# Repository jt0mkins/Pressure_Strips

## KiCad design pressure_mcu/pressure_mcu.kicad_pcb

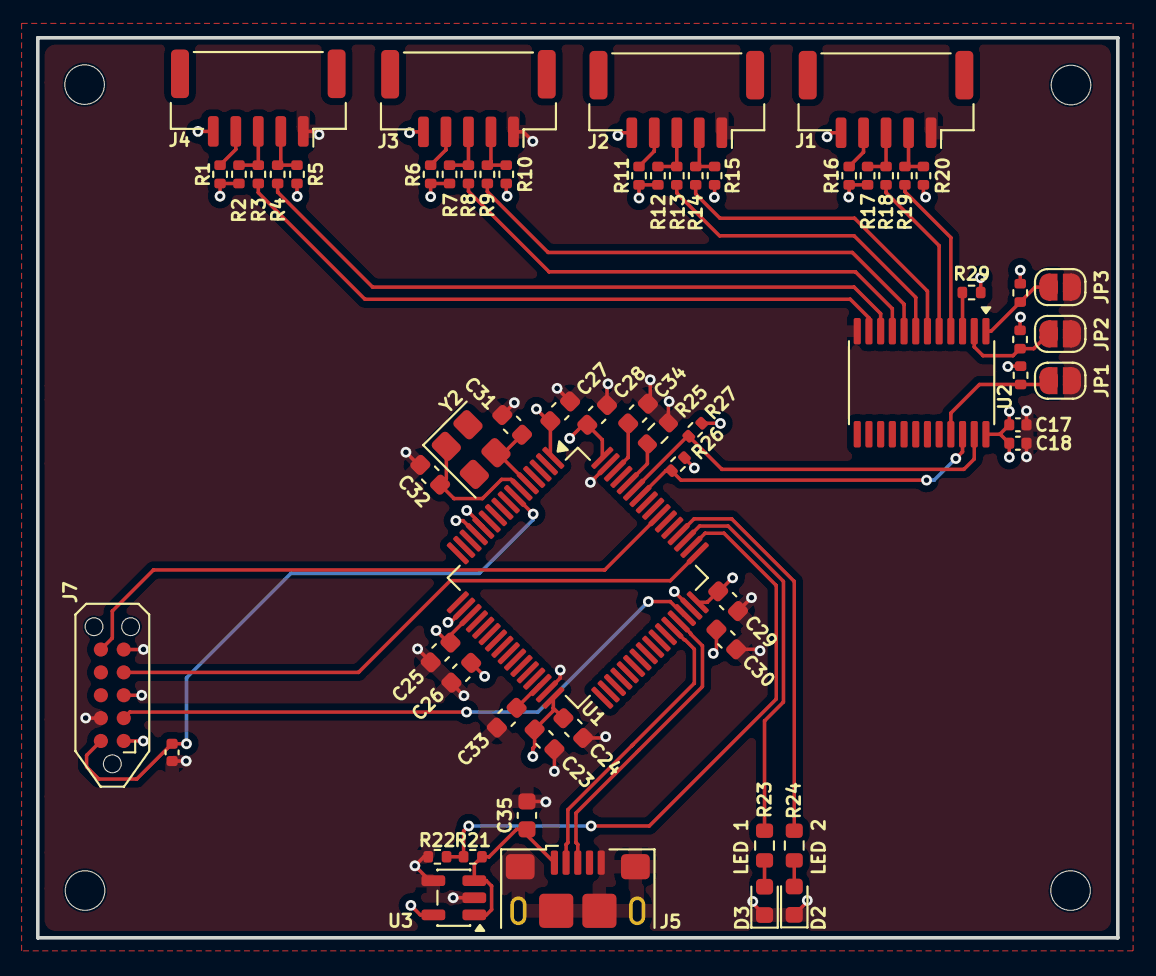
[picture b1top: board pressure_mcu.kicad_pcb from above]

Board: 4 copper layers, 60.0 x 50.0 mm, 66 parts (0 on the bottom side), 45 nets.

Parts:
C17: 4.7uF; C_0402_1005Metric
C18, C36: 100nF; C_0402_1005Metric
C23, C25, C27, C29: 100nF; C_0603_1608Metric
C24, C26, C28, C30: 4.7uF; C_0603_1608Metric
C31, C32: 33pF; C_0603_1608Metric
C33, C34: 2.2uF; C_0603_1608Metric
C35: 10uF; C_0603_1608Metric
D2: LED_R; LED_0603_1608Metric
D3: LED_G; LED_0603_1608Metric
H1, H2, H3, H4: MountingHole; MountingHole_2.2mm_M2
J1: 1; JST_GH_SM05B-GHS-TB_1x05-1MP_P1.25mm_Horizontal
J2: 2; JST_GH_SM05B-GHS-TB_1x05-1MP_P1.25mm_Horizontal
J3: 3; JST_GH_SM05B-GHS-TB_1x05-1MP_P1.25mm_Horizontal
J4: 4; JST_GH_SM05B-GHS-TB_1x05-1MP_P1.25mm_Horizontal
J5: USB_B_Micro; USB_Micro-B_Amphenol_10118193-0001LF_Horizontal
J7: SWD JST PH; Tag-Connect_TC2050-IDC-NL_2x05_P1.27mm_Vertical_with_bottom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
JP1, JP2, JP3: SolderJumper_2_Open; SolderJumper-2_P1.3mm_Open_RoundedPad1.0x1.5mm
R1, R6, R11, R16, R21, R29, R30, R31, R32: 10k; R_0402_1005Metric
R2, R5, R7, R10, R12, R15, R17, R20, R26, R27: 2.2k; R_0402_1005Metric
R3, R4, R8, R9, R13, R14, R18, R19: 0; R_0402_1005Metric
R22: 15k; R_0402_1005Metric
R23, R24: 220R; R_0603_1608Metric
R25: 10k; R_0603_1608Metric
U1: STM32H562RGT6; LQFP-64_10x10mm_P0.5mm
U2: TCA9548APWR; TSSOP-24_4.4x7.8mm_P0.65mm
U3: AP2112K-3.3; SOT-23-5
Y2: 12MHz; Crystal_SMD_Abracon_ABM8G-4Pin_3.2x2.5mm

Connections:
+3V3: C17.1, C18.1, C23.1, C24.1, C25.1, C26.1, C27.1, C28.1, C29.1, C30.1, J1.5, J2.5, J3.5, J4.5, J7.1, R1.1, R2.1, R5.1, R6.1, R7.1, R10.1, R11.1, R12.1, R15.1, R16.1, R17.1, R20.1, R26.1, R27.1, R29.1, R30.1, R31.1, R32.1, U1.1 (VBAT), U1.13 (VDDA), U1.19 (VDD), U1.32 (VDD), U1.48 (VDD), U1.64 (VDD), U2.24 (VCC), U3.5 (VOUT)
/A0: JP3.2 (B), R30.2, U2.1 (A0)
/A1: JP2.2 (B), R31.2, U2.2 (A1)
/A2: JP1.2 (B), R32.2, U2.21 (A2)
/LED1: R23.1, U1.51 (PC10)
/LED2: R24.1, U1.52 (PC11)
/MUX1_NRST: J2.4, R11.2
/MUX1_SCL: J2.3, R12.2, R13.2
/MUX1_SDA: J2.2, R14.2, R15.2
/MUX2_NRST: J1.4, R16.2
/MUX2_SCL: J1.3, R17.2, R18.2
/MUX2_SDA: J1.2, R19.2, R20.2
/MUX3_NRST: J3.4, R6.2
/MUX3_SCL: J3.3, R7.2, R8.2
/MUX3_SDA: J3.2, R9.2, R10.2
/MUX4_NRST: J4.4, R1.2
/MUX4_SCL: J4.3, R2.2, R3.2
/MUX4_SDA: J4.2, R4.2, R5.2
/MUX_NRST: R29.2, U2.3 (~RESET)
/MUX_SCL: R26.2, U1.58 (PB6), U2.22 (SCL)
/MUX_SDA: R27.2, U1.59 (PB7), U2.23 (SDA)
/SWCLK: J7.4, U1.49 (PA14(JTCK)
/SWDIO: J7.2, U1.46 (PA13(JTMS)
/SWO: J7.6, U1.55 (PB3(JTDO)
/USB_D+: J5.3 (D+), U1.45 (PA12)
/USB_D-: J5.2 (D-), U1.44 (PA11)
/V_BUS: C35.1, J5.1 (VBUS), R21.1, U3.1 (VIN), U3.3 (EN)
/V_SENSE: R21.2, R22.1, U1.50 (PA15(JTDI))
/nRESET: C36.2, J7.10, U1.7 (NRST)
GND: C17.2, C18.2, C23.2, C24.2, C25.2, C26.2, C27.2, C28.2, C29.2, C30.2, C31.1, C32.2, C33.2, C34.2, C35.2, C36.1, D2.1 (K), D3.1 (K), J1.1, J2.1, J3.1, J4.1, J5.5 (GND), J5.SH (Shield), J7.3, J7.5, J7.9, JP1.1 (A), JP2.1 (A), JP3.1 (A), R22.2, R25.2, U1.12 (VSSA), U1.18 (VSS), U1.31 (VSS), U1.47 (VSS), U1.63 (VSS), U2.12 (GND), U3.2 (GND), U3.4 (GND)
unnamed: C33.1, U1.30 (VCAP)
unnamed: C34.1, U1.62 (VCAP)
unnamed: D2.2 (A), R24.2
unnamed: D3.2 (A), R23.2
unnamed: R25.1, U1.60 (BOOT0)
unnamed: C31.2, U1.5 (PH0), Y2.3 (2)
unnamed: C32.1, U1.6 (PH1), Y2.1
unnamed: R18.1, U2.5 (SC0)
unnamed: R13.1, U2.7 (SC1)
unnamed: R8.1, U2.9 (SC2)
unnamed: R3.1, U2.11 (SC3)
unnamed: R19.1, U2.4 (SD0)
unnamed: R14.1, U2.6 (SD1)
unnamed: R9.1, U2.8 (SD2)
unnamed: R4.1, U2.10 (SD3)

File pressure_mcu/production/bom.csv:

Designator,Footprint,Quantity,Value,LCSC Part #
C17,0402,1,4.7uF,
"C18, C36",0402,2,100nF,
"C23, C25, C27, C29",0603,4,100nF,C16194197
"C24, C26, C28, C30",0603,4,4.7uF,C907917
"C31, C32",0603,2,33pF,C909846
"C33, C34",0603,2,2.2uF,C77047
C35,0603,1,10uF,
D2,0603,1,LED_R,C23070302
D3,0603,1,LED_G,C20433785
J1,JST_GH_SM05B-GHS-TB_1x05-1MP_P1.25mm_Horizontal,1,1,
J2,JST_GH_SM05B-GHS-TB_1x05-1MP_P1.25mm_Horizontal,1,2,
J3,JST_GH_SM05B-GHS-TB_1x05-1MP_P1.25mm_Horizontal,1,3,
J4,JST_GH_SM05B-GHS-TB_1x05-1MP_P1.25mm_Horizontal,1,4,
J5,USB_Micro-B_Amphenol_10118193-0001LF_Horizontal,1,USB_B_Micro,
J7,Tag-Connect_TC2050-IDC-NL_2x05_P1.27mm_Vertical_with_bottom_clip,1,SWD JST PH,
"R1, R11, R16, R21, R29, R30, R31, R32, R6",0402,9,10k,
"R10, R12, R15, R17, R2, R20, R26, R27, R5, R7",0402,10,2.2k,
"R13, R14, R18, R19, R3, R4, R8, R9",0402,8,0,
R22,0402,1,15k,
"R23, R24",0603,2,220R,C2484076
R25,0603,1,10k,RC0603FR-0710KL
U1,LQFP-64_10x10mm_P0.5mm,1,STM32H562RGT6,C19711662
U2,TSSOP-24_4.4x7.8mm_P0.65mm,1,TCA9548APWR,
U3,SOT-23-5,1,AP2112K-3.3,
Y2,Crystal_SMD_Abracon_ABM8G-4Pin_3.2x2.5mm,1,12MHz,ABM8G-12.000MHZ-18-D2Y-T

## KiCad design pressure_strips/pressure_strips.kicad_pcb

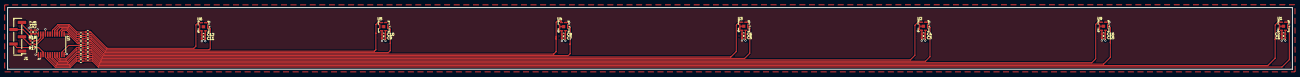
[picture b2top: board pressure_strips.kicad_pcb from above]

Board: 4 copper layers, 357.3 x 17.2 mm, 41 parts (0 on the bottom side), 35 nets.

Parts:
C1, C4, C6, C8, C10, C12, C16, C18: 100nF; C_0402_1005Metric
C2, C3, C5, C7, C9, C11, C15, C17: 4u7F; C_0402_1005Metric
J1: Conn_01x05; PinHeader_1x05_P2.00mm_Vertical_SMD_Pin1Left
R1, R2, R3, R4, R5, R6, R7, R8, R9, R10, R11, R12, R13, R14: R; R_0402_1005Metric
R17, R18: 2.2k; R_0402_1005Metric
U1, U2, U3, U4, U5, U6, U9: ILPS28QSW; ST_CCLGA-7L_2.8x2.8mm_P1.15mm_H1.95mm
U7: TCA9548APWR; TSSOP-24_4.4x7.8mm_P0.65mm

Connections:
+3V3: C1.1, C2.1, C3.1, C4.1, C5.1, C6.1, C7.1, C8.1, C9.1, C10.1, C11.1, C12.1, C15.1, C16.1, C17.1, C18.1, J1.5, U1.6 (VDD), U2.6 (VDD), U3.6 (VDD), U4.6 (VDD), U5.6 (VDD), U6.6 (VDD), U7.24 (VCC), U9.6 (VDD)
/MUX_NRST: J1.2, U7.3 (~RESET)
/MUX_SCL: J1.3, R17.2
/MUX_SDA: J1.4, R18.2
/Sensor0_SCL: R1.2, U1.3 (SCL)
/Sensor0_SDA: R2.2, U1.1 (SDA)
/Sensor1_SCL: R3.2, U9.3 (SCL)
/Sensor1_SDA: R4.2, U9.1 (SDA)
/Sensor2_SCL: R5.2, U2.3 (SCL)
/Sensor2_SDA: R6.2, U2.1 (SDA)
/Sensor3_SCL: R7.2, U3.3 (SCL)
/Sensor3_SDA: R8.2, U3.1 (SDA)
/Sensor4_SCL: R9.2, U4.3 (SCL)
/Sensor4_SDA: R10.2, U4.1 (SDA)
/Sensor5_SCL: R11.2, U5.3 (SCL)
/Sensor5_SDA: R12.2, U5.1 (SDA)
/Sensor6_SCL: R13.2, U6.3 (SCL)
/Sensor6_SDA: R14.2, U6.1 (SDA)
GND: C1.2, C2.2, C3.2, C4.2, C5.2, C6.2, C7.2, C8.2, C9.2, C10.2, C11.2, C12.2, C15.2, C16.2, C17.2, C18.2, J1.1, U1.2 (AH1/QVAR1), U1.4 (AH2/QVAR2), U1.5 (GND), U1.7 (PAD2LID), U2.2 (AH1/QVAR1), U2.4 (AH2/QVAR2), U2.5 (GND), U2.7 (PAD2LID), U3.2 (AH1/QVAR1), U3.4 (AH2/QVAR2), U3.5 (GND), U3.7 (PAD2LID), U4.2 (AH1/QVAR1), U4.4 (AH2/QVAR2), U4.5 (GND), U4.7 (PAD2LID), U5.2 (AH1/QVAR1), U5.4 (AH2/QVAR2), U5.5 (GND), U5.7 (PAD2LID), U6.2 (AH1/QVAR1), U6.4 (AH2/QVAR2), U6.5 (GND), U6.7 (PAD2LID), U7.1 (A0), U7.2 (A1), U7.12 (GND), U7.21 (A2), U9.2 (AH1/QVAR1), U9.4 (AH2/QVAR2), U9.5 (GND), U9.7 (PAD2LID)
unnamed: R1.1, U7.5 (SC0)
unnamed: R3.1, U7.7 (SC1)
unnamed: R5.1, U7.9 (SC2)
unnamed: R7.1, U7.11 (SC3)
unnamed: R9.1, U7.14 (SC4)
unnamed: R11.1, U7.16 (SC5)
unnamed: R13.1, U7.18 (SC6)
unnamed: R17.1, U7.22 (SCL)
unnamed: R2.1, U7.4 (SD0)
unnamed: R4.1, U7.6 (SD1)
unnamed: R6.1, U7.8 (SD2)
unnamed: R8.1, U7.10 (SD3)
unnamed: R10.1, U7.13 (SD4)
unnamed: R12.1, U7.15 (SD5)
unnamed: R14.1, U7.17 (SD6)
unnamed: R18.1, U7.23 (SDA)

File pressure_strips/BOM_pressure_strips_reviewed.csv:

Reference,Qty,Value,Description,Package,Manufacturer,MPN,LCSC,Voltage / Rating,Tolerance / Spec,Datasheet,Notes
"U1,U2,U3,U4,U5,U6,U8,U9",8,ILPS28QSW,"Absolute digital barometric pressure sensor, dual FS (1260/4060 hPa), I2C / MIPI I3C, Qvar",HCLGA-7L 2.8x2.8x1.95mm,STMicroelectronics,ILPS28QSW (reel: ILPS28QSWTR),C5267414,1.7-3.6 V (abs max ~4.8 V),Pressure abs. accuracy +/-0.5 hPa,https://www.st.com/resource/en/datasheet/ilps28qsw.pdf,"Fixed I2C address 0x5C (no SA0 pin) - reason the mux is needed. U8 is in the schematic but NOT placed on the PCB. AH1/AH2->GND OK when Qvar unused (AN5778); also write reg 0x5F=0x00 in FW. PAD2LID->GND OK."
U7,1,TCA9548APWR,"8-channel bidirectional I2C/SMBus switch with reset",TSSOP-24,Texas Instruments,TCA9548APWR,C130026,1.65-5.5 V,-,https://www.ti.com/lit/ds/symlink/tca9548a.pdf,"A0/A1/A2 = GND -> address 0x70 (same as MCU-board mux; OK behind the upstream mux). RESET (pin 3) floating - add 10k to 3V3."
"C1,C4,C6,C8,C10,C12,C14,C16,C18",9,100 nF,"MLCC, VDD decoupling (one per sensor + one at mux)",0402,Yageo / Samsung,CC0402KRX7R7BB104,verify (e.g. C15850),16 V (>=6.3 V),X7R,-,"C14 is missing from production/bom.csv (stale). Place one 100 nF at each ILPS28QSW VDD and at U7 VCC."
"C2,C3,C5,C7,C9,C11,C13,C15,C17",9,4.7 uF,"MLCC, bulk decoupling (one per sensor + one at mux)",0402,Samsung,CL05A475MP5NRNC,C23733,10 V,X5R,-,"C13 is missing from production/bom.csv (stale). 4.7 uF in 0402 derates heavily with DC bias - effective C may be ~1-2 uF; acceptable for decoupling. Consider 0603 if space allows."
"R1,R2,R3,R4,R5,R6,R7,R8,R9,R10,R11,R12,R13,R14,R15,R16",16,0 R (TBD),"Resistor, per-sensor I2C SDA/SCL series (mux channel -> sensor)",0402,UNI-ROYAL,0402WGF0000TCE,C17168,-,-,-,"Value was 'R' (undefined). R15/R16 (Sensor 7) are missing from production/bom.csv. 0R default; 22-100R only if used for edge-rate control. NOT a substitute for pull-ups."
R17,1,0 R (was 2.2 k),"Resistor, I2C main-bus link (J1 SCL -> U7 SCL)",0402,UNI-ROYAL,0402WGF0000TCE,C17168,-,-,-,"WAS 2.2k in series in the bus - wrong. Make 0R or DNP. If a per-strip SCL pull-up is wanted, add a separate R to 3V3."
R18,1,0 R (was 2.2 k),"Resistor, I2C main-bus link (J1 SDA -> U7 SDA)",0402,UNI-ROYAL,0402WGF0000TCE,C17168,-,-,-,"WAS 2.2k in series in the bus - wrong. Make 0R or DNP."
J1,1,1x5 conn,"Board connector to MCU board (3V3, GND, SDA, SCL, NRST)",Currently PinHeader_1x05_P2.00mm_Vertical_SMD,-,pick to mate MCU J4-J7,-,-,-,-,"MISMATCH: schematic uses a 2.00 mm pin header; production/bom.csv says JST EH 2.50 mm; MCU board uses Wuerth WR-WTB 1.50 mm. Choose ONE mating pair for both boards."
